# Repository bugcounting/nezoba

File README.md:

# Nez-Oba: a custom button-only game controller

The Nez-Oba[^1] project provides the schematics of a fully-programmable
all-button wired game controller board, as well as software to program
the controller's behavior to emulate a standard gamepad, and to
reconfigure its button layout.

The controller software works with Nintendo Switch (as a Pro
Controller), as well as with PC/Raspberry PI (as a generic USB
controller). While it can be used, in principle, for any game, it is
primarily intended to play 2D games that require precise button and
D-pad input &mdash; such as platformers.

## Why a custom controller?

Proficiency at 2D platforming games (Super Mario Maker 2, Celeste,
Super Meat Boy, Levelhead, Super Mario Bros. Wonder, Slime-san, Super
One More Jump, ...)  requires being able to precisely enter complex
button and directional inputs. A standard gamepad is not ideal for
this because:[^2]

- It usually has membrane button switches, which provide a suboptimal
  feedback and may not be as precise as mechanical switches.
  
- Its button layout requires to frequently move fingers (especially
  thumbs) from one button to the other. In contrast, an
  all-button/button-only/[hitbox style
  controller](https://ougaming.com/3/7198/a-quick-look-at-the-hitbox-vs-arcade-stick-de)
  minimizes hand and finger movement, and simplifies reliably entering
  complex presses.

There are numerous all-button controllers for PCs, and a few even work
with the Nintendo Switch. In particular, I like the [Junk Food
Arcades' Snack Box
Micro](https://junkfoodarcades.com/collections/snack-box-micro), as
well as [8bitdo's Arcade Stick](https://www.8bitdo.com/arcade-stick/)
[modded](https://www.youtube.com/watch?v=Yn7xL-vFdPc) with
[MyrzArcade's L-shaped
T-Spin](https://www.etsy.com/listing/733030620/t-spin-pcb-only-diy-tetromino-shaped)
(see also [OmniArcade's Odin](https://www.etsy.com/shop/OmniArcade) if
you like the WASD layout). The [Edgeguard keyboard
adapter](https://keyboard.gg/) also looks great. However, none of
these options supports switching between different programmable button
layouts without reconfiguring the board's software; their default
layout is not ideal for games like SMM2; and the distance between
buttons is somewhat wide, which can make repeatedly pressing certain
button combinations unconformable in the long run.

Hence, I went down this rabbit hole starting in the fall of 2021. The
first (and, so far, only) two fully working Nez-Oba game controllers
were completed in March 2022, and I've been using them with gusto ever
since.

After that, I worked on and off to improve the software, develop a
usable web-based GUI for definining the custom mappings, and to
provide detailed documentation. While there are still plenty of things
that could be improved, this is the first public release of the whole
project.[^3]

This is what the Nez-Oba game controller looks like IRL (this is the
version with black case and red linear Kahil low-profile switches):

Its main features:

- Game controller board with twelve mechanical switches (as well as
  three auxiliary switches) and tight, comfortable physical layout.
  
- Fully remappable layout with capacity to store sixteen different
  button-to-key-press mappings.

- Each physical button can map to a combination of up to three
  simultaneous key presses.
  
- Support for turbo functionality (fast repeated key presses).

## Usage

The Nez-Oba projects includes both hardware and software components.

### Build the board

Under [hw/kicad/](/hw/kicad/) you will find:

- PCB schematics of the Nez-Oba board and how to manufacture them

- A list of components that have to be soldered onto the board

You will also need a USB-micro-to-USB-A cable to connect the board's
controller to the Switch or PC.

### Print the case

Under [hw/case/](/hw/case/) you will find 3D models of a case for
the game controller board, which you can 3D-print.

### Install the software

The Nez-Oba software is actually in two parts:

- An Arduino project in C/C++ with the software that runs on the
  board's microcontroller.
  
- A Python project to configure the button-to-key-press mappings that
  the on-board software supports.
  
The Python project is the single entry point to all software, since it
also provides commands to configure, compile, and upload the
microcontroller software.

You install this software as a regular Python project. As usual, it's
recommended that you create a virtual environment to install
dependencies more easily:

```sh
python3 -m venv venv
source vent/bin/activate
python3 -m pip install --upgrade pip
```

Then, there are different options to install the software:

1. Directly from GitHub:

```sh
python3 -m pip install git+https://github.com/bugcounting/nezoba
```

2. From a local copy the Git repository:

```sh
git clone https://github.com/bugcounting/nezoba
cd nezoba
python3 -m pip install .
```

3. From the release wheel:

Download
[/releases/latest/](latest
release wheel `nezoba*.whl`) and install it:

```sh
python3 -m pip install "$NEZOBA.whl"
```

You can also avoid downloading dependencies by using the
[/releases/latest/](`nezoba*.wheels.tgz`):

```sh
tar xf "$NEZOBA.wheels.tgz"
python3 -m pip install wheels/nezoba-*.whl --find-links=./wheels
```

### Use the software

Command `nezoba` is the entry point for using the whole
software. Start with `nezoba -h`.

A common workflow:

1. Have a look at the default button-to-key-presses mappings that I
   defined for 2d platformers: `nezoba show`.
   
2. If you want to define your own mappings, start the GUI with:
    `nezoba gui` (the GUI will appear at
    `http://127.0.0.1:8000/`). Alternatively, there's a simpler CLI
    shell that supports similar functionality: `nezoba cli $MAPPINGS_YAML`.
	
3. Setup the Arduino compiler and libraries with `nezoba setup
   "$SYSTEM_DIR"`, where `$SYSTEM_DIR` is the directory where you want
   to install them.
   
   Alternatively, among the [/releases/latest/](release files) you
   will also find an archive `arduino-cli-4nez.tar.xz` that includes a
   fully setup environment for Linux systems. Unpacking the content of
   that archive under `$SYSTEM_DIR` is an equivalent way of setting up
   your system.
   
4. Deploy the controller's software with your YAML mappings
   `$MAPPINGS`: `nezoba deploy "$SYSTEM_DIR" "$MAPPINGS"`. If you omit
   `$MAPPINGS`, the default mappings for 2d platformers will be
   deployed.
   
The `deploy` command will finally upload to the board. For this to
work, the board has to be plugged in to a USB port of the computer,
and it may have to be reset. See the [troubleshooting
section](/src/README.md#upload-troubleshooting) for a few practical
tips.
   
### Testing/development

If you want to test the installation of the Nez-Oba software, and
possibly change or extend its functionalities:

```sh
# Install the `test` target in editable mode
python3 -m pip install -e .[test]
# Run the Python tests
cd test/nezoba
pytest .
# Run the Arduino software tests
cd test/board
make test
./test
```

[^1]: What does the acronym "Nez-Oba" mean? I'm afraid I don't
    remember :-/

[^2]: Of course, top players make the most out of regular
    controller. On the other hand,
    [Niftski](https://en.wikipedia.org/wiki/Niftski), the
    [top](https://www.youtube.com/watch?v=i_9Hj--VfbY) Mario
    Bros. speedrunner at the time of writing, often uses a mechanical
    keyboard!

[^3]: The dev repository includes nearly 900 commits in 120 days over
    more than 3 years!

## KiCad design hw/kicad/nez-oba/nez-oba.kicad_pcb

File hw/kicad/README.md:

# The Nez-Oba controller board

This directory schematics and assembly instructions for the Nez-Oba
game controller board, which can be manufactured as a PCB and then
programmed using the software available [elsewhere](/src/) in this
repository.

The board's design is defined in a [KiCad](https://www.kicad.org/)
(version 5.1.5) project including a schematics, a PCB layout, and
symbol and footprint libraries to make the project self-contained.

## Components

The PCB mounts the following components:

   - An Adafruit [Trinket M0](https://www.adafruit.com/product/3500)
     development board, which runs the controller software.
	 
   - An MCP 23017 port expander, which communicates with the Trinket
     through a clocked serial line. The expander supports 16
     independent digital inputs, which are needed for the many
     buttons of the controller.
	 
   - A piano-type 4-bit DIP switch, which stores the controller's
     configuration number (which, in turn, determines the mapping of
     buttons to gamepad keys).
	 
   - 12 mechanical switches, meant for the 4 directional inputs and 8
     main gamepad buttons.
	 
   - Another 3 switches, meant for the 3 auxiliary gamepad buttons
     (such as *select* and *start*).
	 
The switches are in two groups because the board uses mechanical
switches for the main buttons, and smaller/cheaper tactile buttons for
the auxiliary buttons. However, they all behave the same (and one
could easily change switch type without having to change the
schematics).

## Schematics
	 
The 15 switches are connected each to a separate input of the
expander.  The mapping switch-to-expander makes it easier to lay out
the tracks in the PCB. However, it's essentially immaterial, since any
remapping can be defined via software.

The 4 pins of the DIP switch are connected to the remaining available
digital inputs: 3 of them connect to pins 1, 4, and 2 of the Trinket;
the last one connects to the last input of the expander.

The rest of the connections complete the schematics:

   - All ground pins connect to the Trinket's `GND` pin, which is
     connected to the USB power's ground (hence, it's an output pin
     for the circuit).
	 
   - The expander's three address pins `A0`, `A1`, and `A2` also
     connect to ground. This corresponds to using the [default
     address](https://www.best-microcontroller-projects.com/mcp23017.html)
     0x20. Adding other I2C devices may require to change the address,
     by setting some of these pins to high.
	 
   - The expander's `VDD` and `RESET` pins connect to the Trinket's
     `USB` pin, which draws 5V from the USB power (hence, it's an
     output pin for the circuit).
	 
   - The expander's clock (`SCL`) and data (`SDA`) pins connect to the
     Trinket's clock (pin 2) and data (pin 0) pins (see the [Trinket's
     pinout](https://learn.adafruit.com/adafruit-trinket-m0-circuitpython-arduino/pinouts)). They
     also connect to 5V each [through
     a](https://learn.adafruit.com/using-mcp23008-mcp23017-with-circuitpython/python-circuitpython)
     4.7k Ohm pullup resistor.

## PCB

The symbols used in the schematics are associated with footprints
suitable for the different components used on the PCB. The symbols
also include information about exact product numbers and
manufacturers, so that it should be possible to generate a BOM (bill
of materials) for automated assembly.

The expander has a footprint for a standard DIP packaging with 28 pins
at 2.54mm-pitch, with a form factor of 36x7.8mm.

The 12 mechanical switches mount [Kailh
Choc](https://www.kailhswitch.com/news/kailh-low-profile-mechanical-switches-series-19669171.html)
low-profile mechanical switches. The pin layout is incompatible with
the more common Cherry MX buttons (or other kinds of high-profile
buttons). However, the footprint's size is the same; hence, it should
not be hard to change the design to accommodate Cherry MX switches.

There are *two* symbols for Kailh switches, one for the red (linear)
switches and one for the white (clicky) ones. They are physically and
functionally identical; I created two symbols only to have a way of
storing manufacturer information for both kinds of switches. Indeed,
you can use any other kind of Kailhs, provided they are low profile.

The 3 auxiliary switches mount the cheap 4-pin tactile button
switches, which are very common in cheap electronics starter kits. The
pair of pins on each side of the switch are connected to each other;
clicking the switch connects the pairs on opposing sides. To make this
clear, the PCB connects the two holes on one side of the footprint
with a track. When soldering the switches, make sure to test which
side is connected!

The front layer mounts all switches: main buttons, auxiliary buttons,
and DIP configuration switch. The back layer mounts the control
electronics: Trinket, expander, and the two pullup resistors. This
layout minimizes the height of the top layer, so that the box can
touch the top layer's surface almost everywhere in a stable way.

Most wiring runs on the bottom layer, with only a few short tracks on
the top layer. Filled zones on the top and bottom layers are connected
to ground, which makes for a simple wiring of all ground pins.

The PCB also includes four 4.5 mm diameter mounting holes, at the four
corners of the board.

### Variants of the expander component

A previous version of the controller board (0.1, which was just a
prototype) used an expander mounted on a terminal breakout board
(usually called an CJMCU 2317). This component has the same pinout
(and behavior) as the MCP 23017 expander, but is wired [slightly
differently](https://www.best-microcontroller-projects.com/mcp23017.html):

   - The expander's clock and data pins do not use pullup resistors:
     they just connect to the Trinket.
	 
   - The expander's `RESET` pin connects to 5V through a 10k Ohm
     resistor.

In the attached library, there are also footprints for two models of
terminal breakout boards (of different widths), which should be
mounted using pin headers. The default, however, is to use the MCP
23017 expander without terminal breakout board.

## Changing the board's layout

If you change anything in the schematics (or PCB):

  1. Run the ERC (Electrical Rules Checks) in the schematics layout
     editor (ladybug icon), to make sure they all pass.
 
  2. In the PCB layout editor, click on *Update PCB from schematic*
     (icon to the left of the ladybug icon)
     
	 - Uncheck *Delete extra footprints*, so that the mounting holes
       are not removed.
	   
     - If you didn't change any references (for example, by changing
       it in the footprint editor) you can select *Re-associate
       footprints by reference*. Note that the footprints in library
       `nez-footprint` are set up so that they do not display the
       reference in the PCB view; instead, they display extra text
       that you can customize to reflect the function of each
       component (e.g., each button's default behavior).
	   
     - Click on *Update PCB* and make sure there are no errors.
	   
  3. If you changed anything in the footprints, select *Tools ->
     Update Footprints from Library*. After clicking on *Apply* there
     should be no errors.
	 
  4. Run the DRC (Design Rules Checks) in the PCB layout
     editor (ladybug icon), to make sure they all pass.
	 
	 - Check *Refill all zones*.
	 
	 - I recommend to check both *Report all errors* and *Test tracks
       against filled copper* to perform all checks. It won't take
       long on this simple PCB.
	   
     - Click on *Run DRC* and make sure there are no errors.

In the PCB layout editor, layer *Dwgs.User* is hidden by default. This
includes outlines of all components, which are useful to re-place
footprints after some significant component change.

## Ordering components

The components' symbols also include a link to a page in Digi-Key's
online catalog.

More directly, here are some suggestions about where to buy the
components (from mostly European distributors, but it should not be
hard to find them elsewhere):

   - Any basic 4.7k Ohm resistor should be fine. 5k Ohm ones should
     also work (although I haven't extensively tested them).

   - The 3 auxiliary switches are very common components. Make sure
     you select some with a sufficiently long button cap, so that it
     reaches out of the case.
	 
   - The 4-bit DIP switch is also very common. Check that its
     footprint fits the enclosing case's hole; height should not be an
     issue.
	 
   - Suppliers of components for mechanical keyboards should have the
     Kailh switches, although the Choc models are a bit less widely
     available. (I bought mine from
     [MyKeyboard](https://mykeyboard.eu/): EUR 11 for 20 switches; but
     this seller is [no longer in
     business](https://www.reddit.com/r/MechanicalKeyboards/comments/1ctgniw/mykeyboard_eu_is_bankrupt/). Alternatively,
     there's [42.keebs](https://42keebs.eu/) which is also EU based.)
	 
   - For the expander, look for MCP23017-E/SP components; "E/SP"
     denotes the packaging that the controller uses. As discussed
     [above](#variants-of-the-expander-component), with the default
     layout you just need the bare component, without any mounting
     socket or terminal breakout board (although adding a socket to
     the design should not be hard). Any online electronics shop
     should have them. (I bought mine on Amazon: EUR 4.)
	 
   - Finally, the Trinket M0 should also not be too hard to find. (I
     bought one of mine on Amazon; another one from
     [Distrelec](https://www.distrelec.ch/), which has online stores
     in various countries: CHF 10.)
	 
Altogether, the bare components should cost around EUR 30 (although
you may have to buy some in bulk, using only a few of them).

## PCB manufacturing

To send the PCB layout for manufacturing you can usually either send
the `.kicad-pcb` file or generate plot and drill files. I'll describe
this second way, which is more widely supported (although most PCB
manufacturers also accept CAD files nowadays).

   1. In KiCad's PCB layout editor, click on *Plot* (plotter icon,
      right of the printer icon).
	  
      - *Plot format*: Gerber
	  
	  - Select the following layers: F.Cu, B.Cu (front and back
        copper), F.SilkS, B.SilkS (front and back silk screen),
        F.Mask, B.Mask (front and back solder masks), and Edge.Cuts
        (the perimeter of the board). 
		
	  - Click on *Plot*. This will generate 7 plot files with
        extension `.gbr` (one per layer).
		
	  - In the same window, click on *Generate Drill Files*, and then
        again *Generate Drill File* in the window that opens. This
        will generate 2 drill files with extension `.drl`: one for
        plated through holes (PTH) and one for non-plated through
        holes (NPTH).
	  	
   2. Create a zip file including all 9 generated files (plot and
      drill files).
	   
   3. On the manufacturer's main page, you usually start by an
      approximate size for the PCB. You can measure it in the PCB
      layout editor with the measure distance tool (calipers icon):
      180x104mm should work for the controller board.
	   
   4. Then you upload the zip file with all plot information, and
      select any other options for manufacturing. Default options
      should be fine for this project.
	   
   5. The manufacturer will then perform additional checks to confirm
      they can manufacture the PCB.

I used [EuroCircuits](https://www.eurocircuits.com/) to manufacture my
two Nez-Oba PCBs. They have reasonable prices and deliver high-quality
boards (but YMMV, of course). I payed around EUR 70 for one PCB,
including shipping costs.

## Soldering components

When you assemble the PCB by soldering the components on it, there are
a few things to pay attention to.

   - The Kailh switches' mounting holes are asymmetric, so there's
     only one way that the switches will fit them.
	 
   - The DIP 4-bit switch can be mounted in either directions, but I
     recommend to mount it so that any text on the PCB (especially the
     bit numbers) is readable in the board's "natural" orientation,
     which is the one where the large writing *NEZ-oba* is readable.
	 
   - As explained above, the 4-pin auxiliary button switches have a
     polarity. Check with a multimeter which pairs of pins are wired
     to each other, and then insert one such pair into the pair of
     mounting holes that are also wired with a track on the top layer
     (red line in the PCB layout editor).
	 
   - The MCP23017 also has a polarity. Its [pin
     #1](https://ww1.microchip.com/downloads/en/devicedoc/20001952c.pdf)
     should be marked with a little dot on the DIP packaging; that pin
     goes into the bottom right mounting hole on the back of the PCB,
     which is also marked with a square pad (instead of circular as
     all other mounting holes), as well as with the writing *B0*.
	 
   - Solder header pins to the Trinket, and then solder the other end
     of the pins onto the bottom of the board. Use the writings on the
     board to properly orient the Trinket. In a nutshell, the
     Trinket's top layer (where the tiny reset button is) should face
     away from the PCB's bottom layer, in a way that the Trinket's
     micro USB port is next to the PCB's top edge.
	 
 If you're not sure, use a breadboard to test the components with the
 software, and then assemble them.

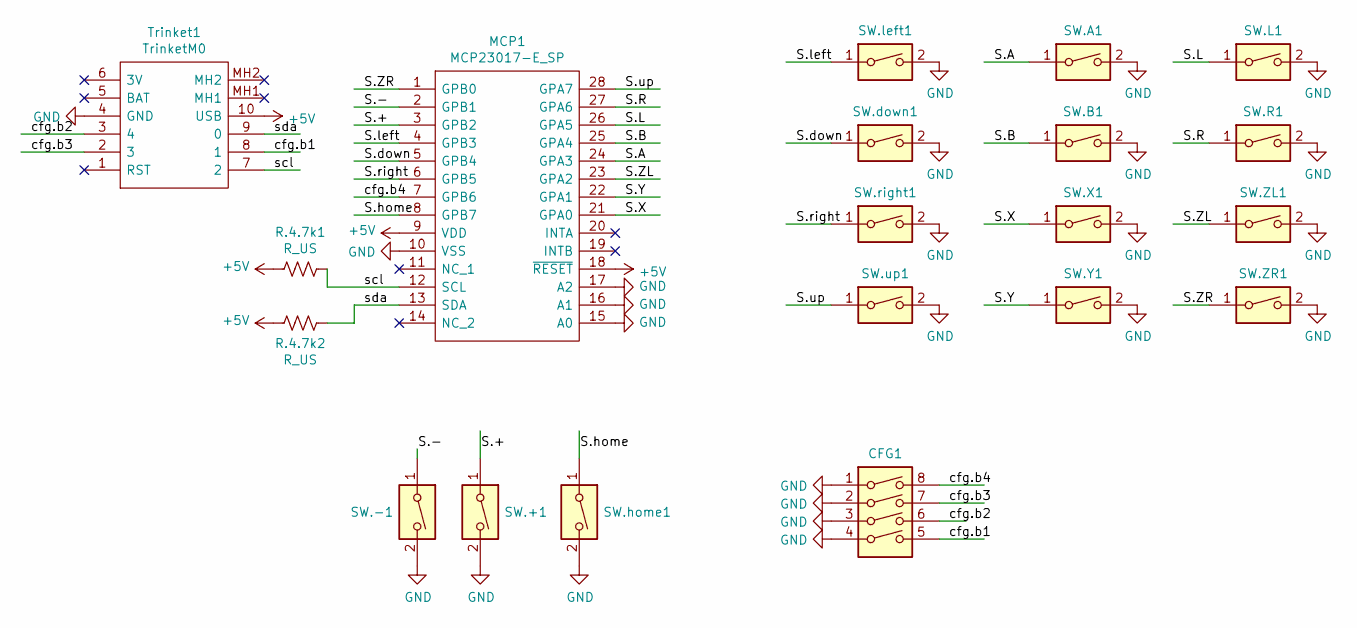
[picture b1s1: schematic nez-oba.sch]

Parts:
CFG1: SW_DIP_x04; SW_DIP_SPSTx04_Slide_6.7x11.72mm_W7.8mm_P2.54mm; Manufacturer_Part_Number KG04E; Digi-Key Part Number 2449-KG04E-ND
MCP1: MCP23017-E_SP; DIP-28_W7.62mm; Manufacturer_Part_Number MCP23017-E/SP; Digi-Key Part Number MCP23017-E/SP-ND
R.4.7k1, R.4.7k2: R_US; R_LDR_P12mm_narrow; Manufacturer_Part_Number ROX1SJ4K7; Digi-Key Part Number A131473CT-ND
SW.+1, SW.-1, SW.home1: SW_DIP_x01_tactile; SW_SPST_B3S-1000; Manufacturer_Part_Number 430476085716; Digi-Key Part Number 430476085716-ND
SW.A1, SW.B1, SW.L1, SW.R1, SW.X1, SW.Y1, SW.ZL1, SW.ZR1, SW.down1, SW.left1, SW.right1, SW.up1: SW_DIP_x01_Kailh_Choc_Red; Kailh_Choc_LowProfile_CPG135001D02; Manufacturer_Part_Number 5113; Digi-Key Part Number 1528-5113-ND
Trinket1: TrinketM0; Trinket_M0; Manufacturer_Part_Number 3500; Digi-Key Part Number 1528-2361-ND

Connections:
+5V: MCP1.9 (VDD), MCP1.18 (~RESET), R.4.7k1.2, R.4.7k2.2, Trinket1.10 (USB)
/S.+: MCP1.3 (GPB2), SW.+1.1
/S.-: MCP1.2 (GPB1), SW.-1.1
/S.A: MCP1.24 (GPA3), SW.A1.1
/S.B: MCP1.25 (GPA4), SW.B1.1
/S.L: MCP1.26 (GPA5), SW.L1.1
/S.R: MCP1.27 (GPA6), SW.R1.1
/S.X: MCP1.21 (GPA0), SW.X1.1
/S.Y: MCP1.22 (GPA1), SW.Y1.1
/S.ZL: MCP1.23 (GPA2), SW.ZL1.1
/S.ZR: MCP1.1 (GPB0), SW.ZR1.1
/S.down: MCP1.5 (GPB4), SW.down1.1
/S.home: MCP1.8 (GPB7), SW.home1.1
/S.left: MCP1.4 (GPB3), SW.left1.1
/S.right: MCP1.6 (GPB5), SW.right1.1
/S.up: MCP1.28 (GPA7), SW.up1.1
/cfg.b1: CFG1.5, Trinket1.8 (1~)
/cfg.b2: CFG1.6, Trinket1.3 (4)
/cfg.b3: CFG1.7, Trinket1.2 (3)
/cfg.b4: CFG1.8, MCP1.7 (GPB6)
/scl: MCP1.12 (SCL), R.4.7k1.1, Trinket1.7 (2)
/sda: MCP1.13 (SDA), R.4.7k2.1, Trinket1.9 (0)
GND: CFG1.1, CFG1.2, CFG1.3, CFG1.4, MCP1.10 (VSS), MCP1.15 (A0), MCP1.16 (A1), MCP1.17 (A2), SW.+1.2, SW.-1.2, SW.A1.2, SW.B1.2, SW.L1.2, SW.R1.2, SW.X1.2, SW.Y1.2, SW.ZL1.2, SW.ZR1.2, SW.down1.2, SW.home1.2, SW.left1.2, SW.right1.2, SW.up1.2, Trinket1.4 (GND)

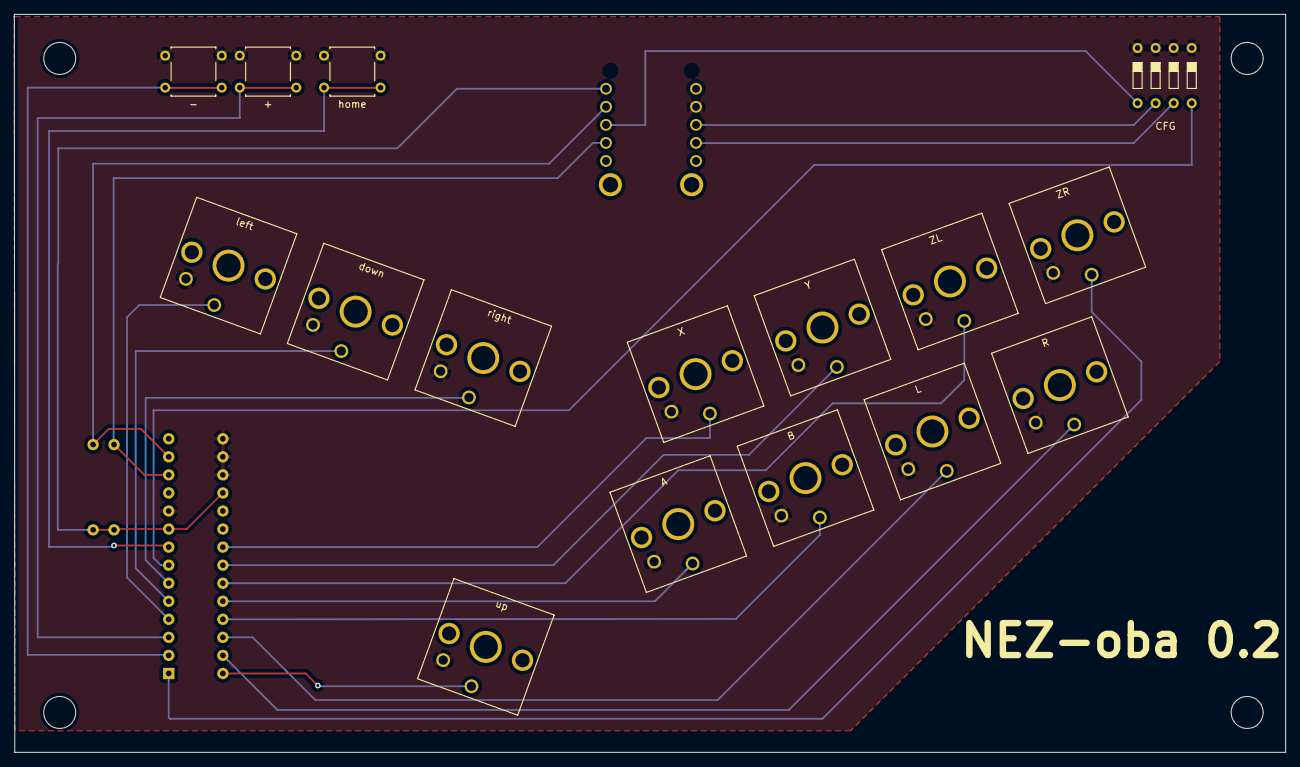
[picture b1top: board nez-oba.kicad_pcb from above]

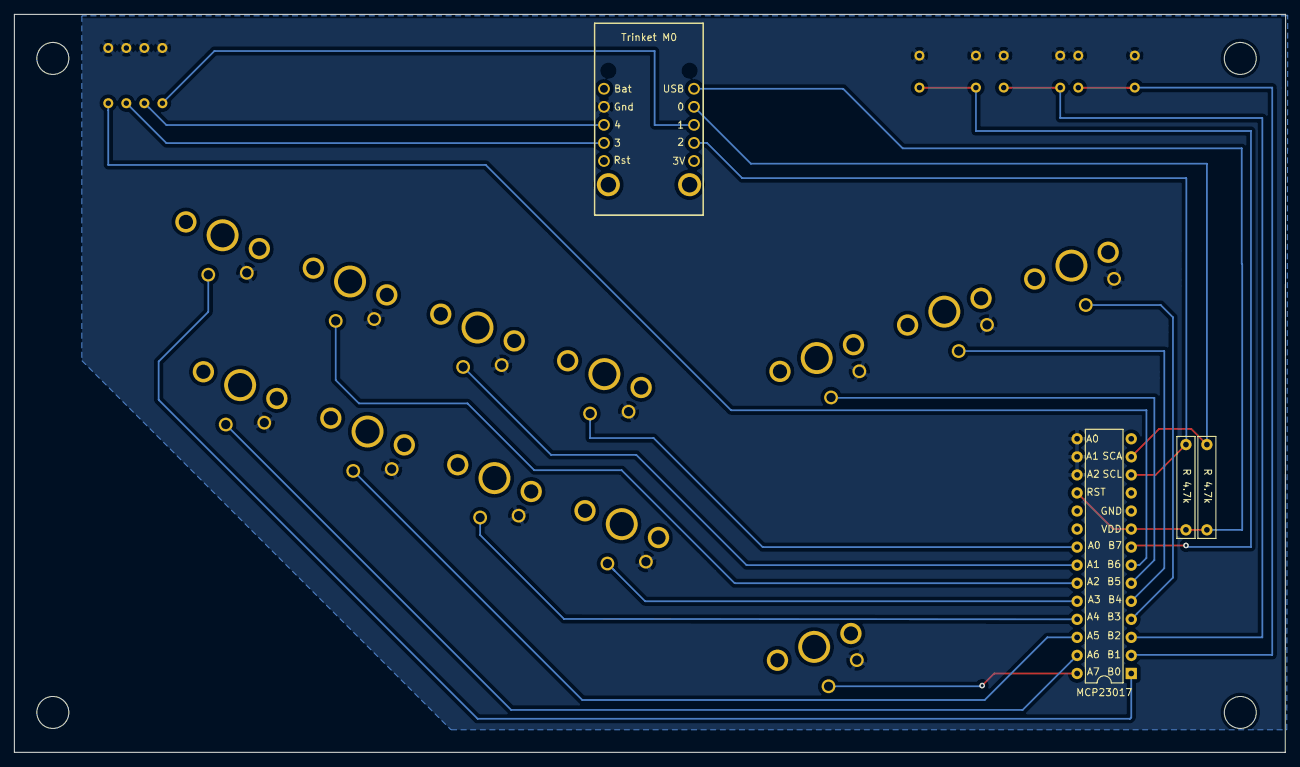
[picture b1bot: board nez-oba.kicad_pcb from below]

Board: 2 copper layers, 178.9 x 103.8 mm, 20 parts (4 on the bottom side), 23 nets.

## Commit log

2025-01-04 Initial commit to initialize the repo.
2025-01-04 Release 2025.1
2025-01-04 Fix typo.
